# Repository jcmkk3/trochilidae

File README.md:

# 🐦trochilidae
A from-scratch re-creation of the [Hummingbird keyboard](https://github.com/PJE66/hummingbird) using ergogen

**NOTE:** *These boards are still a work-in-progress. They are awaiting the last few adjustments before the final routing and slikscreens are added.*

## The Family
### Rufous
*Selasphorus rufus*

This board is the basis of all other boards in this repo. It is modeled after the original hummingbird.

### Berylline
*Saucerottia beryllina*

This board features some adjustments to the key placement from the Rufous
- A slight increase in angle between the halves 23 -> 25 degrees
- 3 degrees of splay between pinky and ring columns
- 2 degrees of splay between ring and middle columns
- Slightly increased stagger for all columns
- Thumb keys are moved slightly towards the center

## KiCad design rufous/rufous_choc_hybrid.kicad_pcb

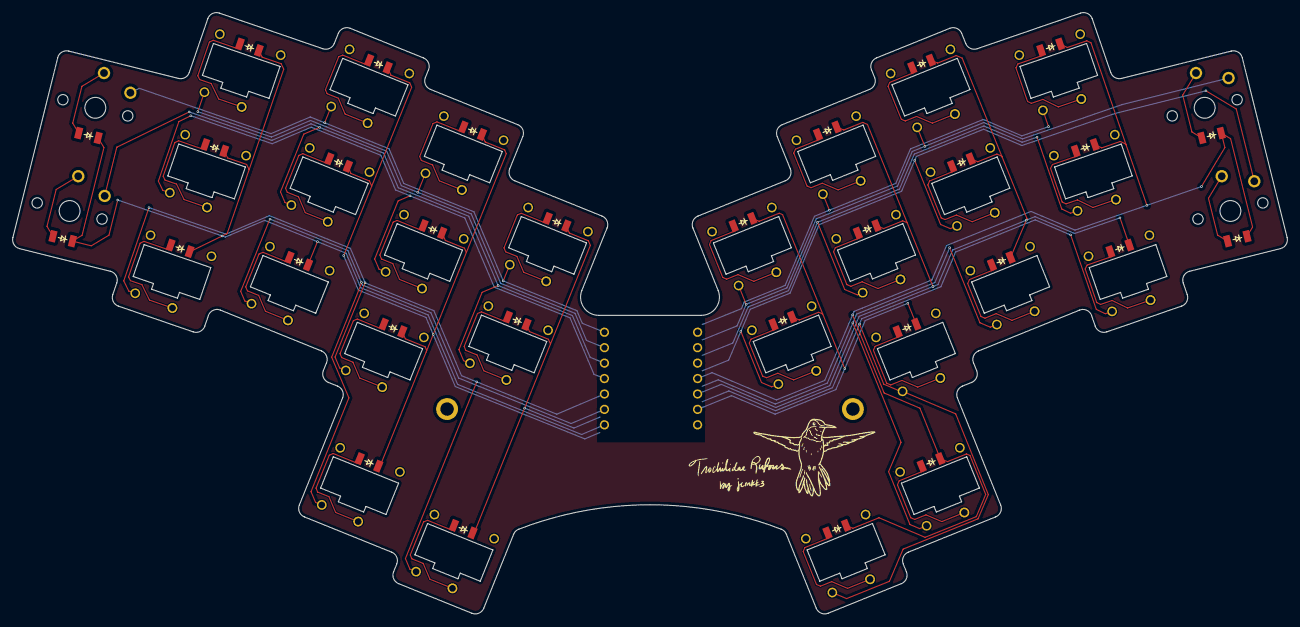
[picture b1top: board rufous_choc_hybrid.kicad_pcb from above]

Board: 2 copper layers, 209.8 x 99.0 mm, 32 parts (0 on the bottom side), 11 nets.

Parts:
HOLE1, HOLE2: M2MountingHoleSlimSimple
S1, S2, S16, S17: ChocSimpleDiode
S3, S4, S5, S6, S7, S8, S9, S10, S11, S12, S13, S14, S15, S18, S19, S20, S21, S22, S23, S24, S25, S26, S27, S28, S29, S30: ChocMiniSimpleDiode

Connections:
P0: S2.1, S8.1, S13.1, S20.1, S26.1
P1: S5.1, S11.1, S17.1, S23.1, S28.1
P2: S1.1, S7.1, S12.1, S19.1, S25.1
P3: S4.1, S10.1, S16.1, S22.1, S27.1
P4: S3.1, S9.1, S15.1, S21.1, S29.1
P5: S6.1, S14.1, S18.1, S24.1, S30.1
P6: S1.2, S2.2, S3.2, S4.2, S5.2, S6.2
P7: S7.2, S8.2, S9.2, S10.2, S11.2, S14.2
P8: S12.2, S13.2, S15.2, S24.2, S27.2, S28.2
P9: S18.2, S21.2, S22.2, S23.2, S25.2, S26.2
P10: S16.2, S17.2, S19.2, S20.2, S29.2, S30.2

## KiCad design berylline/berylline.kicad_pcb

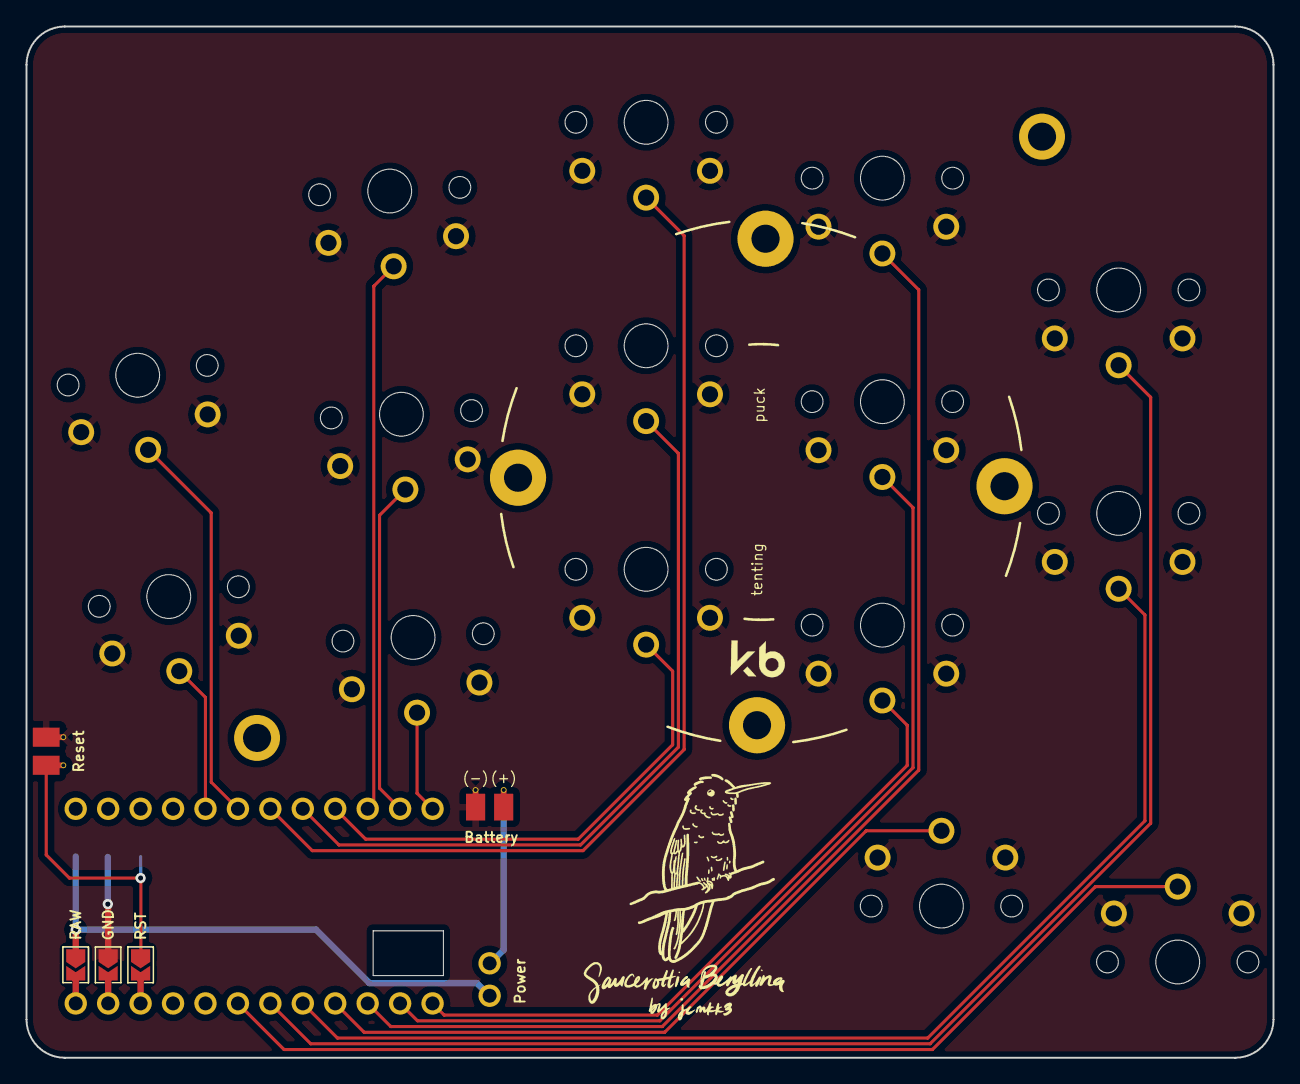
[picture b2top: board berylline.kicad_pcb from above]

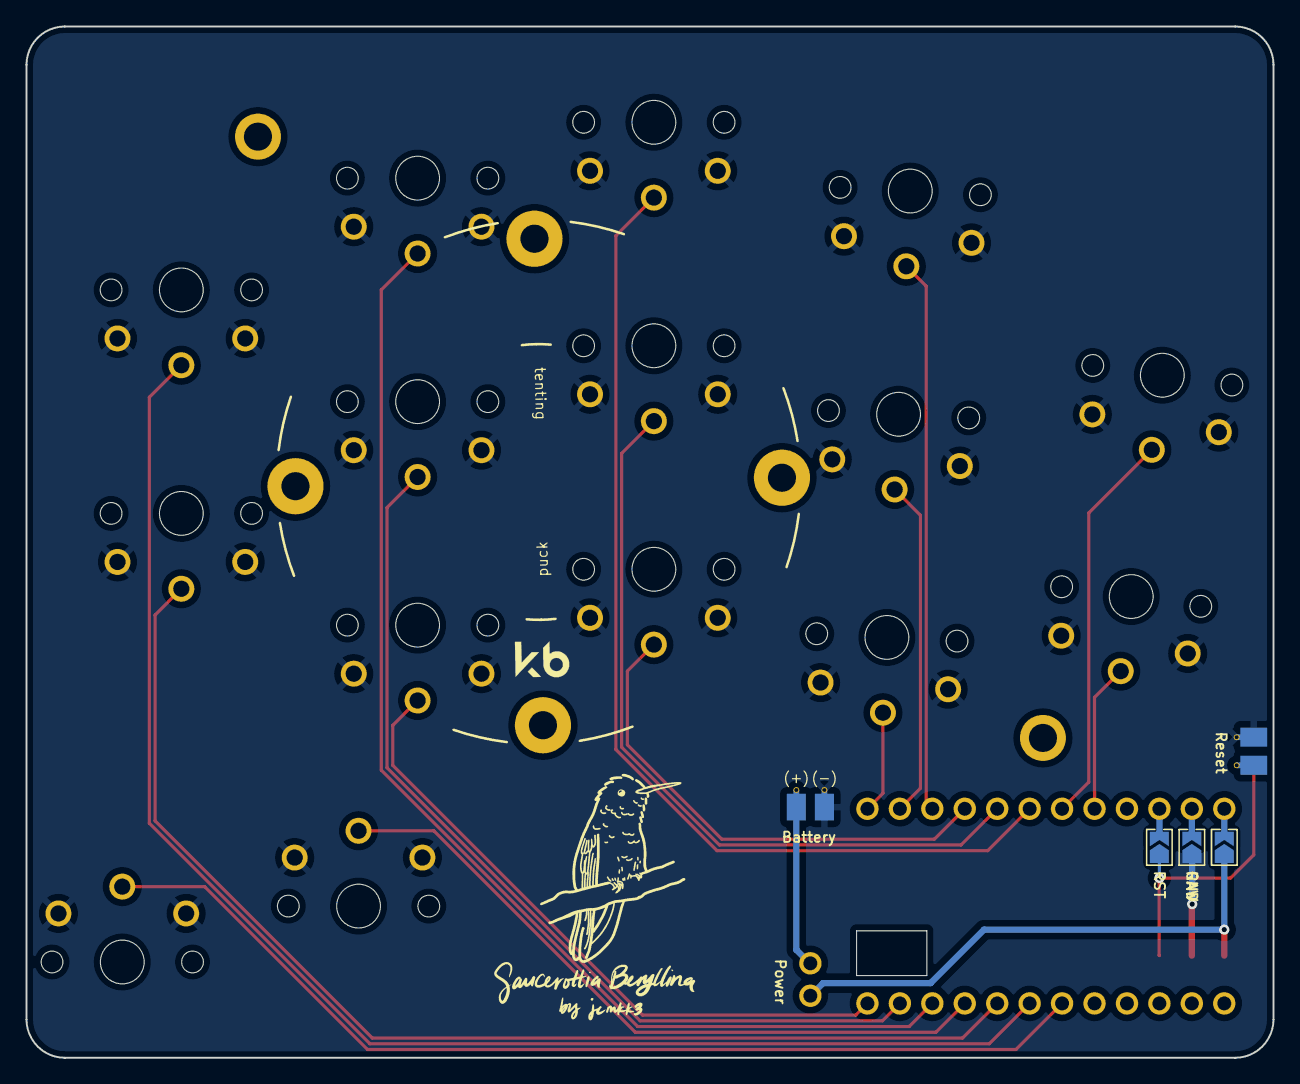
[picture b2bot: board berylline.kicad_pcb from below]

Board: 2 copper layers, 97.6 x 80.8 mm, 19 parts (3 on the bottom side), 18 nets.

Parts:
J1: Val**; HeaderJumperSimple
J2, J3: Battery_Cell; Battery_pads_reversible
MCU1: ProMicroSimpleJumper
S1, S2, S3, S4, S5, S6, S7, S8, S9, S10, S11, S12, S13, S14, S15: PG1350Reversible

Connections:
GND: J2.2, J3.2, MCU1.2, S1.1, S2.1, S3.1, S4.1, S5.1, S6.1, S7.1, S8.1, S9.1, S10.1, S11.1, S12.1, S13.1, S14.1, S15.1
P3: MCU1.18, S15.2
P4: MCU1.19, S13.2
P5: MCU1.20, S12.2
P6: MCU1.21, S14.2
P7: MCU1.22, S11.2
P8: MCU1.23, S10.2
P9: MCU1.24, S9.2
P10: MCU1.12, S3.2
P14: MCU1.10, S5.2
P15: MCU1.9, S6.2
P16: MCU1.11, S4.2
P18: MCU1.8, S7.2
P19: MCU1.7, S8.2
P20: MCU1.6, S2.2
P21: MCU1.5, S1.2
RAW: J1.1, J1.2, J2.1, MCU1.1
RST: J3.1, MCU1.3

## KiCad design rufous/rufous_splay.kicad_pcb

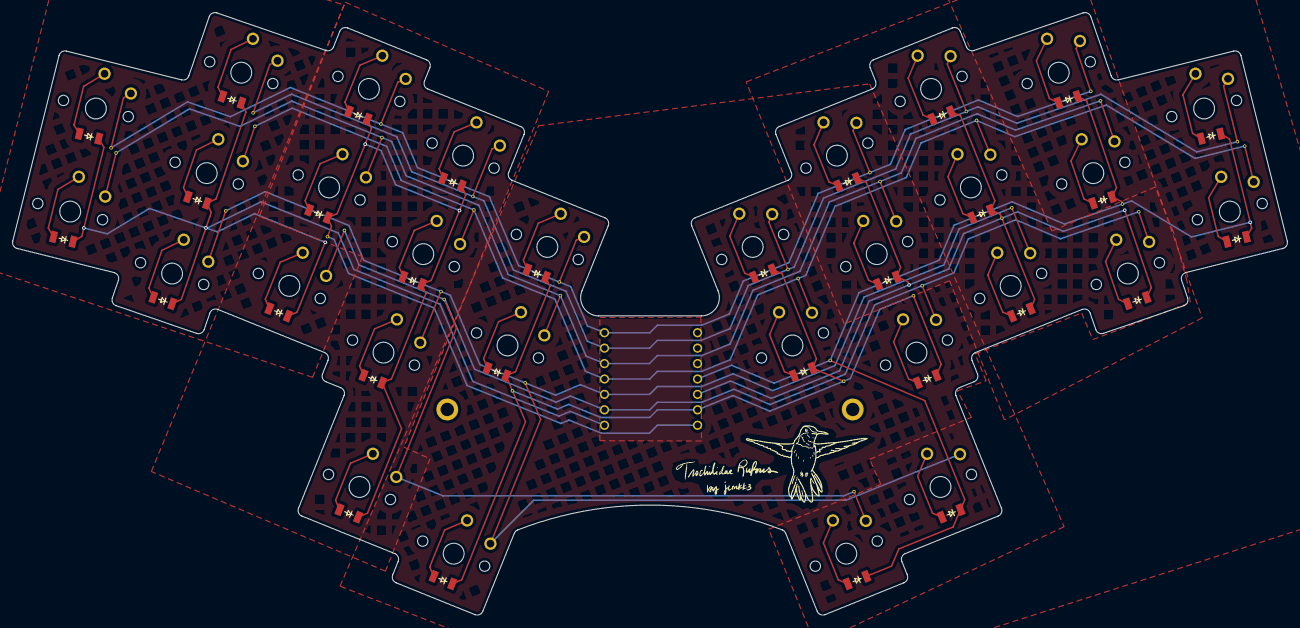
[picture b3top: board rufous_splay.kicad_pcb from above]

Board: 2 copper layers, 210.0 x 99.2 mm, 62 parts (0 on the bottom side), 41 nets.

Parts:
D1, D2, D3, D4, D5, D6, D7, D8, D9, D10, D11, D12, D13, D14, D15, D16, D17, D18, D19, D20, D21, D22, D23, D24, D25, D26, D27, D28, D29, D30: BigDiode
HOLE1, HOLE2: M2MountingHoleSimple
S1, S2, S3, S4, S5, S6, S7, S8, S9, S10, S11, S12, S13, S14, S15, S16, S17, S18, S19, S20, S21, S22, S23, S24, S25, S26, S27, S28, S29, S30: PG1350

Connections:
P0: S2.1, S8.1, S13.1, S20.1, S26.1
P1: S5.1, S11.1, S17.1, S23.1, S28.1
P2: S1.1, S7.1, S12.1, S19.1, S25.1
P3: S4.1, S10.1, S16.1, S22.1, S27.1
P4: S3.1, S9.1, S15.1, S21.1, S29.1
P5: S6.1, S14.1, S18.1, S24.1, S30.1
P6: D1.1, D2.1, D3.1, D4.1, D5.1, D6.1
P7: D7.1, D8.1, D9.1, D10.1, D11.1, D14.1
P8: D12.1, D13.1, D15.1, D24.1, D27.1, D28.1
P9: D18.1, D21.1, D22.1, D23.1, D25.1, D26.1
P10: D16.1, D17.1, D19.1, D20.1, D29.1, D30.1
index_bottom: D9.2, S9.2
index_home: D10.2, S10.2
index_top: D11.2, S11.2
inner_home: D12.2, S12.2
inner_thumb: D15.2, S15.2
inner_top: D13.2, S13.2
middle_bottom: D6.2, S6.2
middle_home: D7.2, S7.2
middle_top: D8.2, S8.2
mirror_index_bottom: D24.2, S24.2
mirror_index_home: D25.2, S25.2
mirror_index_top: D26.2, S26.2
mirror_inner_home: D27.2, S27.2
mirror_inner_thumb: D30.2, S30.2
mirror_inner_top: D28.2, S28.2
mirror_middle_bottom: D21.2, S21.2
mirror_middle_home: D22.2, S22.2
mirror_middle_top: D23.2, S23.2
mirror_outer_thumb: D29.2, S29.2
mirror_pinky_home: D16.2, S16.2
mirror_pinky_top: D17.2, S17.2
mirror_ring_bottom: D18.2, S18.2
mirror_ring_home: D19.2, S19.2
mirror_ring_top: D20.2, S20.2
outer_thumb: D14.2, S14.2
pinky_home: D1.2, S1.2
pinky_top: D2.2, S2.2
ring_bottom: D3.2, S3.2
ring_home: D4.2, S4.2
ring_top: D5.2, S5.2

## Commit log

2021-10-16 Create simple.yml
    The most simple config to create the hummingbird physical layout
2021-10-16 Clean up simple and add spread to rows and columns
2021-10-16 Create 01_with_point_nets
2021-10-16 Rename simple.yml to 00_simple.yml
2021-10-16 Rename 01_with_point_nets to 01_with_point_nets.yml
2021-10-17 Reformat - unnest for ease of reading
2021-10-17 Fix the thumb connections
2021-10-17 Add rounded corners
2021-10-17 Fix top glue portion
2021-10-18 Attempt at bottom center section
    This is getting somewhere, but I'm not sure that I like the approach.
2021-10-18 Proper fix for bottom and top center
2021-10-18 Make distance between halves a fixed value
2021-10-18 Fix cx/cy comments
2021-10-18 Change to single sided diodes in switch footprint
2021-10-18 Position the MCU
2021-10-19 Adjust binding
2021-10-19 Add switch plate
2021-10-19 Tweak switchplate
2021-10-19 Slight refactoring
2021-10-19 Improve binds
2021-10-19 Adjust thumb cluster vertical stagger
2021-10-20 Fix nets orientation on footprints
2021-10-21 Adjust angle to match hummingbird
2021-10-21 Adjust switch footprint size
2021-10-21 Refactor center outline
    Remove the glue feature and use polygon instead for more control of positioning
2021-10-21 Increase top-center fillet size
2021-10-21 Adjust mirroring config
2021-10-21 Adjust top-center spacing
2021-10-22 Fix MCU (xiao) placement
2021-10-22 Adjust footprint spacing
2021-10-22 Adjust diode and thumb placement
2021-10-22 Adjust top center spacing/fillet
2021-10-22 Create chopped_and_screwed
    Some initial exploration of splay and more aggressive stagger
2021-10-22 Rename chopped_and_screwed to chopped_and_screwed.yml
2021-10-22 Move thumb cluster in and halves out slightly
2021-10-22 Increase angle between halves slightly
2021-10-22 Slightly reduce ring - index stagger
2021-10-24 Simplify units
    Remove some units that were only used in a few places. Also changed the binds to be larger to better deal with different splays.
2021-10-24 Add splay adjustment for pinky and ring
2021-10-25 Cleaned up center a bit and confirmed bottom arc radius
    Measured bottom arc radius on hummingbird and confirmed that it was around 60
2021-10-25 Fix binds so none break through the edges at certain splay
2021-10-25 Rename 03_with_pcb.yml to base.yml
2021-10-25 Rename base.yml to rufous/config.yml
2021-10-25 Rename chopped_and_screwed.yml to berylline/config.yml
2021-10-25 Fix diode direction
2021-10-25 Add pictures!
2021-10-25 Rename todos.org to TODOS.org
2021-10-25 Rename TODOS.org to TODO.org
2021-10-25 Use shortened version of outlines
2021-10-25 Move footprint config at key level down near pcb section
2021-10-25 Add more comments to document the config
2021-10-25 Adjust angle to reflect original hummingbird
2021-10-25 Change distance between sides anchor and value
2021-10-25 Adjust origin of 2 row columns
2021-10-25 Slight adjustment to alignment caused by changing to glue
2021-10-25 Remove glue again
    Remove glue that was added in commit: 5ede06017c979f48422cca1b3838f6223ac0dc91
2021-10-26 Clarify in comments
2021-10-26 Remove unneeded parenthesis
2021-10-26 Fix comment to remove glue reference
2021-10-26 Change pcb output name to match board name
2021-10-26 Keep up with changes from rufous
2021-10-26 Adjust some alignment to use sf instead of cx/cy
2021-10-27 Add information about future boards
2021-10-27 Add awesome artwork by perce
2021-10-28 Switch from diode footprint to 2 pads for more control
2021-10-28 Add mounting holes for case
2021-10-28 Back to regular diode footprint
2021-10-29 Add vias for row routing
    Will need some more thinking/work to get positioning right
2021-10-29 Improve middle column via positions
2021-10-29 Adjust height and add pinky vias
2021-10-29 Adjustments to via positions
    Left side is close to dialed in!
2021-10-29 Fix right side via positions
2021-10-31 Clean up existing vias and add bottom vias
2021-11-01 Incorporate changes from rufous
2021-11-01 Remove origin from pinky and inner columns
2021-11-02 Create new folder
2021-11-20 Add pretty OSH Park generated previews
2021-11-20 Reduce image size
2021-11-21 First attempt at a case
2021-11-21 Refine case
2021-11-21 Parameterize rim width
2021-11-21 Rearrange to keep PCB related items closer to each other
2021-11-22 Update footprint files
2021-11-29 More aggressive splay/stagger/angle/thumb position
2021-12-31 Slight tweaks from base config
2021-12-31 Adjust origin to even up column spacing
2021-12-31 Update renders
2022-01-01 Update images to reflect changes in routing
2022-01-01 Update to reflect rufous splay
2022-01-01 Add proper nets and mcu position
2022-01-01 Swap pinky nets for better routing
2022-01-02 Adjust nets and mcu position
2022-01-02 Initial placement of reset, battery, and power
2022-01-02 More component adjustments
2022-01-04 Rename workshop/split-square.yml to berylline/config.yml
2022-01-04 Update/add footprints
2022-01-04 Add kicad file
2022-01-04 Remove a couple of case mounts
2022-01-05 Add kicad file in main repo
2022-01-05 Update pcb image
2022-01-05 Add berylline information
2022-01-05 Fix mcu silkscreen
2022-01-06 Reflect silkscreen fix
2022-01-14 Increase outline fillet size
2022-01-15 Refactor berylline
2022-01-15 Naming cleanups
2022-01-15 Reorder some rows to be consistent
2022-01-15 Fix weird formatting issue
2022-01-15 Add outline extents
2022-01-24 More explicit naming
2022-01-24 Position components relative to mcu
2022-01-24 Simplify berylline (#5)
    * Update config.yml
    * More explicit naming
    * Position components relative to mcu
2022-01-24 Add photos of built boards
2022-01-24 Use different photo of rufous
2022-01-24 Better photo
2022-01-24 Remove future variants section
2022-01-25 Remove placeholder. Will be a rufous variant instead
2022-01-25 Create LICENSE
2022-02-13 Use generic kx/ky units
2022-02-13 Reduce duplication
2022-02-13 Clean up outlines
2022-02-13 Rely on default operation
2022-02-13 Add keycap demo
2022-02-13 Cleanup whitespace
2022-02-13 Name thumbs to remove rows
2022-02-13 Comment visual xy
2022-02-13 Reorder rows to follow bottom/home/top
2022-02-13 Rotate thumbs
2022-02-14 Different approach to thumb key rotation
2022-02-23 Rufous cleanup and pre-release
2022-02-24 Fix commented out lines
2022-02-24 Cleanup extraneous comments
2022-02-24 What happens when you rotate the keys?
2022-02-24 Clean up row-stagger
2022-02-25 Change to promicro and current config structure
2022-02-25 First try at pin assignment
2022-02-25 row_net correction
2022-02-26 Better net assignments
2022-02-27 Rename square-tight.yml to square-tight-promicro.yml
2022-03-13 Rename berylline config to fit new pattern
2022-03-13 Update footprints
2022-03-13 Correct net for thumbs
2022-03-13 Update kicad files
2022-03-15 Add switchplates
2022-03-18 Clean up footprints
2022-03-19 Use actual MX values
2022-04-20 Create choc-min-spacing
2022-04-20 Less vertical space for thumb cluster
2022-04-22 Rename choc-min-spacing to choc-min-spacing.yml
2022-04-22 Add base neblina config
2022-04-22 Back to tight edge cuts
2022-04-23 horizontal xiao
2022-04-24 Add placeholder nets
2022-04-24 Cleanup config
2022-04-24 Add additional footprints
2022-04-25 Add rest of components
2022-04-25 Add battery cutout
2022-04-25 Refactor berylline and add berylline_choc_min
2022-04-25 Add beryllin_mx_min
2022-04-25 Add mx and choc minimum spacing versions of berylline
2022-04-25 Swap nets on reset and battery
2022-04-26 Fix berylline mx min to have middle splay
2022-04-26 Shift thumb slightly
2022-04-26 Tweak middle splay and thumb offset
2022-05-02 Rename reviung.yml to simple_reviung41.yml
2022-05-02 Formatting fixes to simple reviung
2022-05-06 Fix nets
2022-05-12 Clean ups to berylline
2022-05-13 Cleanup berylline
2022-05-13 Cleanups to berylline
    - Slightly adjust battery cutout
    - Improve reproducibility by removing some manual adjustments in kicad step
2022-05-13 Update footprints to latest
2022-06-02 Create wubbo_mod.yml
    Based on the wubbo by cache, modded to mx min-spacing, broom thumbs, using a xiao (eventually)
2022-06-02 Add key demo
2022-06-02 Tweaks to outline and thumbs
2022-06-03 Create fancy_hummingbird.yml
    This is a variation of the hummingbird for `fancytapwater` from Absolem Club
2022-06-03 Polish up 1.5u key visual and spacing
2022-06-03 Modify edge cuts for 1.5u keys
2022-06-03 Fix mounting hole placement
2022-06-04 Add second bottom row option
2022-06-05 Lots of tweaks
2022-06-05 Add pcb
2022-06-06 Add outline
2022-06-08 Fix inadvertent commit
2022-06-14 Different approach to row stagger
2022-06-16 Fix stagger
2022-07-31 Add berylline chocV2 config
2023-04-11 Update berylline choc to v4
2023-05-02 More updating for v4
2023-05-16 Add meta section
2023-05-16 Shift mcu back to edge
2023-05-16 Increase spacing between switches and outline
2023-05-16 Consistent partial units and reduce duplication
2023-05-16 Reorder mcu nets
2023-05-16 Cleanup comments
2023-05-16 More streamlining
2023-05-16 Remove nesting level from pcbs
2023-05-16 Add presets section to consolidate spacing variations
2023-05-16 Rename berylline_choc.yml -> berylline.yml and remove other variations
2023-05-16 Berylline v4 update (#11)
    * Update berylline choc to v4
    * Add meta section
    * Increase spacing between switches and outline
    * Add presets section to consolidate spacing variations
2023-05-17 Add battery connector
2023-05-18 Add reset placement
2023-05-18 Swap nets on reset
2023-05-20 Update reset for optional switch
2023-05-22 Adjust reset placment
2023-05-22 Update mcu pinout
2023-06-16 Add minimal_panel
2023-06-16 Position mcu
2023-06-16 Change mcu type and position
2023-06-16 Add initial nets
2023-06-21 Minor spacing changes
2023-06-21 Add explaination
2023-06-22 Revert pinky spread limit
2023-06-22 Add MX preset and back to tight edgecuts
2023-06-26 Add some additional outlines for visualization
2023-06-27 First parts of case
2023-06-27 More complete case
2023-07-02 Finish rufous upgrade to ergogen v4
2023-07-02 Remove kicad files and pcb renders
2023-07-02 Move spread and padding to top level keys
2023-07-03 Consistent use of where and adjust
2023-07-04 Add usb cutout
2023-07-05 Update center top edge cut to use a reference point
2023-07-05 Tweak usb cutout
2023-07-14 Additional panel shape
2023-07-14 Edge cut tweaks
2023-07-14 Lots of refactoring
2023-07-17 Make switchplate larger than panel, add demo_all
2023-07-18 Revert some unintended changes when upgrading to v4
2023-07-18 Initial neblina config
2023-07-18 Add power switch
2023-07-19 Remove power switch, add usb cutout
2023-07-19 Adjustments to ensure usb fits
2023-07-19 More precise xiao position
2023-07-19 Better mounting hole placement
2023-07-19 Remove fillet, causing artifacts
2023-07-27 Move filleting to the _switches step
2023-07-28 Add defaults to presets section
2024-06-05 Fix rufous to work with 4.1
2024-06-12 Different take on namesake
2025-01-31 xiao + joycon battery
2025-03-10 Initial changes to accomodate mixed spacing
2025-03-10 Slight tweaks to keycap shifts
2025-05-06 Tighten spacing
2025-05-06 Tighter edge cuts vertically
2025-05-07 Adjust edge cuts to align with keycaps for maximum pcb space for switches
2025-05-18 More adjustments
2025-05-18 Refine how key positions adapt to different spacings
    Key positions for the choc version remain the same, but other spacings will change slightly.
2025-05-18 Reset footprints back
2025-05-18 Bump rufous version
